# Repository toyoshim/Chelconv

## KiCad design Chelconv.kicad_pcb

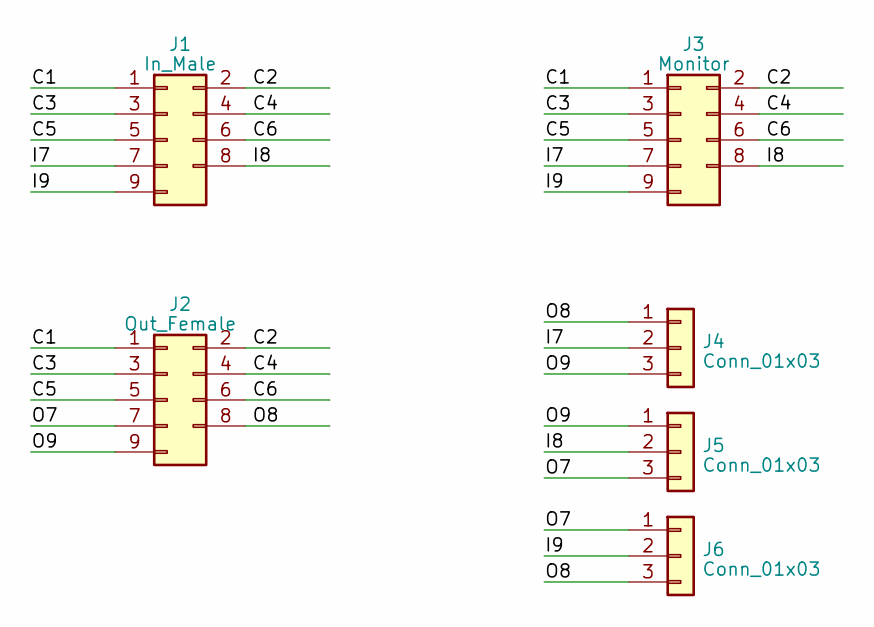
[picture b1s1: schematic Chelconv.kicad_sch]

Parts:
J1: In_Male; DSUB-9P-Male-FOXCONN_DT10121
J2: Out_Female; DSUB-9_Female_TE_2301844_1
J3: Monitor; PinHeader_2x05_P2.54mm_Vertical
J4, J5, J6: Conn_01x03; PinHeader_1x03_P2.54mm_Vertical

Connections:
/C1: J1.1, J2.1, J3.1
/C2: J1.2, J2.2, J3.2
/C3: J1.3, J2.3, J3.3
/C4: J1.4, J2.4, J3.4
/C5: J1.5, J2.5, J3.5
/C6: J1.6, J2.6, J3.6
/I7: J1.7, J3.7, J4.2
/I8: J1.8, J3.8, J5.2
/I9: J1.9, J3.9, J6.2
/O7: J2.7, J5.3, J6.1
/O8: J2.8, J4.1, J6.3
/O9: J2.9, J4.3, J5.1

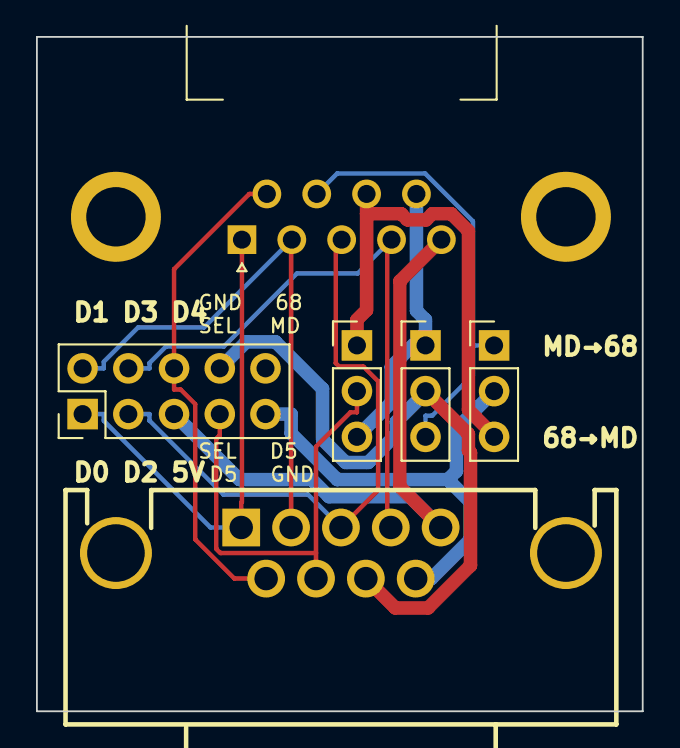
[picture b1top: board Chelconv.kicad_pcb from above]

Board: 2 copper layers, 33.7 x 37.5 mm, 6 parts (0 on the bottom side), 12 nets.
